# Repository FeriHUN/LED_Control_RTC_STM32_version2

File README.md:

# LED_Control_RTC_STM32_version2
20 channel 16 bit PWM LED strip brightness controller for 12-24V applications with RS485 connectivity

[Expander board link](https://github.com/FeriHUN/LED_Control_RTC_STM32_version2_Expander)

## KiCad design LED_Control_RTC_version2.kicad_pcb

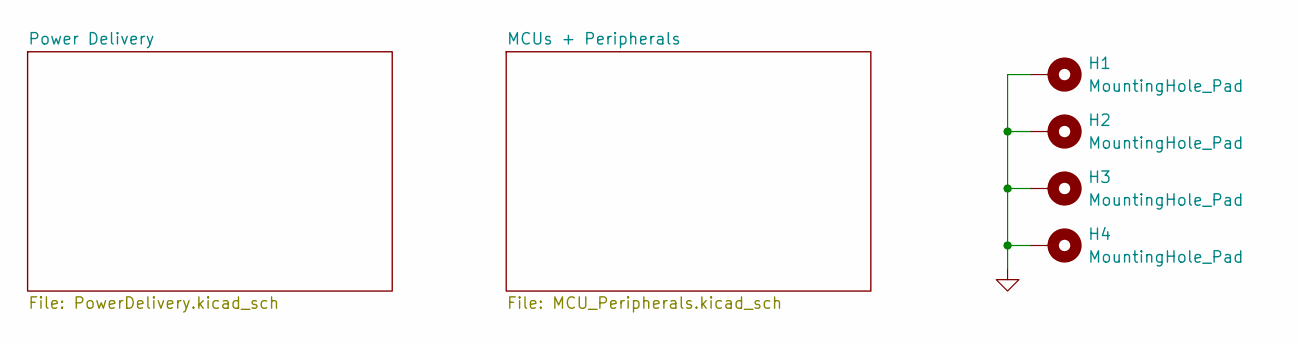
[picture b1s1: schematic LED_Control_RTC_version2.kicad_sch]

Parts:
H1, H2, H3, H4: MountingHole_Pad; MountingHole_3.2mm_M3_Pad_Via

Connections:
GND: H1.1, H2.1, H3.1, H4.1; also elsewhere on the board

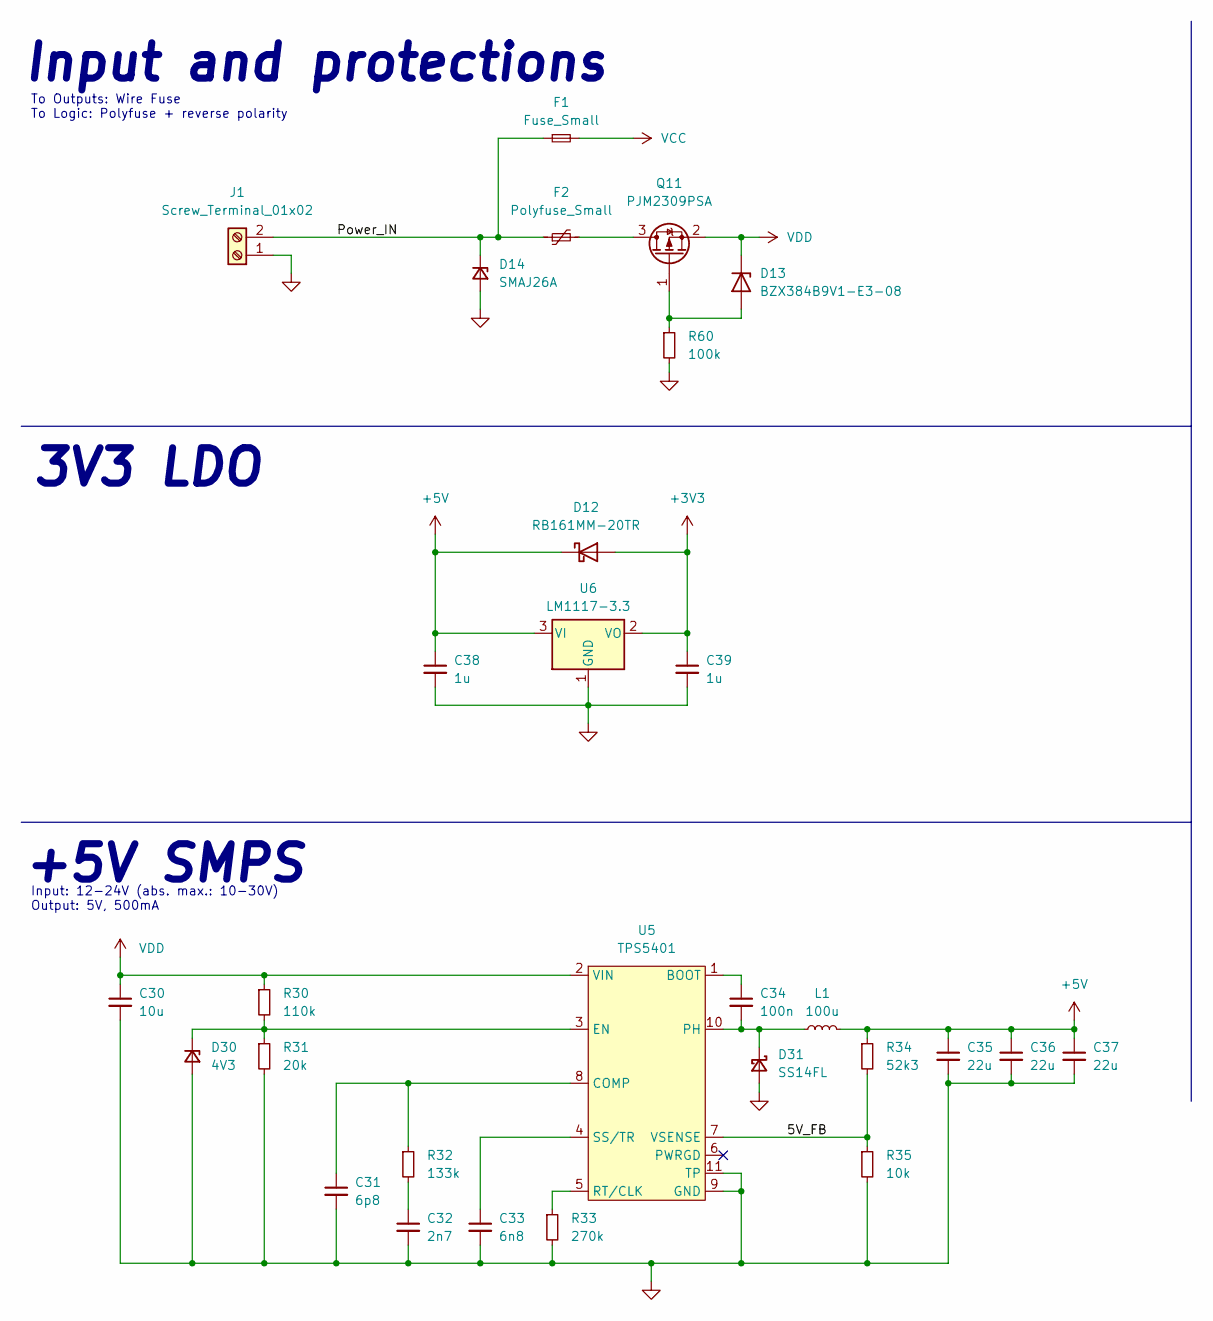
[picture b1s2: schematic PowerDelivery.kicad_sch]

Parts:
C30: 10u; R_1206_3216Metric
C31: 6p8; R_0603_1608Metric
C32: 2n7; R_0603_1608Metric
C33: 6n8; R_0603_1608Metric
C34: 100n; R_0603_1608Metric
C35, C36, C37: 22u; R_1206_3216Metric
C38, C39: 1u; C_0603_1608Metric
D12: RB161MM-20TR; D_SOD-123F
D13: BZX384B9V1-E3-08; D_SOD-323
D14: SMAJ26A; D_SMA
D30: 4V3; D_SOD-123
D31: SS14FL; D_SMA
F1: Fuse_Small; Fuseholder_Littelfuse_100_series_5x20mm
F2: Polyfuse_Small; Fuse_1812_4532Metric
J1: Screw_Terminal_01x02; PhoenixContact_MC_1,5_2-GF-5.08_1x02_P5.08mm_Horizontal_Thr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
L1: 100u; ABG08A40M101
Q11: PJM2309PSA; SOT-23
R30: 110k; R_0603_1608Metric
R31: 20k; R_0603_1608Metric
R32: 133k; R_0603_1608Metric
R33: 270k; R_0603_1608Metric
R34: 52k3; R_0603_1608Metric
R35: 10k; R_0603_1608Metric
R60: 100k; R_0402_1005Metric
U5: TPS5401; MSOP-10-1EP_3x3mm_P0.5mm_EP1.68x1.88mm_ThermalVias
U6: LM1117-3.3; SOT-223-3_TabPin2

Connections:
+5V: C35.1, C36.1, C37.1, C38.1, D12.1 (K), L1.2, R34.1, U6.3 (VI); also elsewhere on the board
/Power Delivery/5V_FB: R34.2, R35.1, U5.7 (VSENSE)
/Power Delivery/Power_IN: D14.1 (K), F1.1, F2.1, J1.2
GND: C30.2, C31.2, C32.2, C33.2, C35.2, C36.2, C37.2, C38.2, C39.2, D14.2 (A), D30.2 (A), D31.2 (A), J1.1, R31.2, R33.2, R35.2, R60.2, U5.9 (GND), U5.11 (TP), U6.1 (GND); also elsewhere on the board
unnamed: C31.1, R32.1, U5.8 (COMP)
unnamed: C32.1, R32.2
unnamed: C33.1, U5.4 (SS/TR)
unnamed: C34.1, U5.1 (BOOT)
unnamed: C34.2, D31.1 (K), L1.1, U5.10 (PH)
unnamed: D13.2 (A), Q11.1 (G), R60.1
unnamed: D30.1 (K), R30.2, R31.1, U5.3 (EN)
unnamed: F2.2, Q11.3 (D)
unnamed: R33.1, U5.5 (RT/CLK)
VCC: F1.2; also elsewhere on the board
VDD: C30.1, D13.1 (K), Q11.2 (S), R30.1, U5.2 (VIN)

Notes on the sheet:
+5V SMPS
Input: 12-24V (abs. max.: 10-30V) Output: 5V, 500mA
3V3 LDO
Input and protections
To Outputs: Wire Fuse To Logic: Polyfuse + reverse polarity

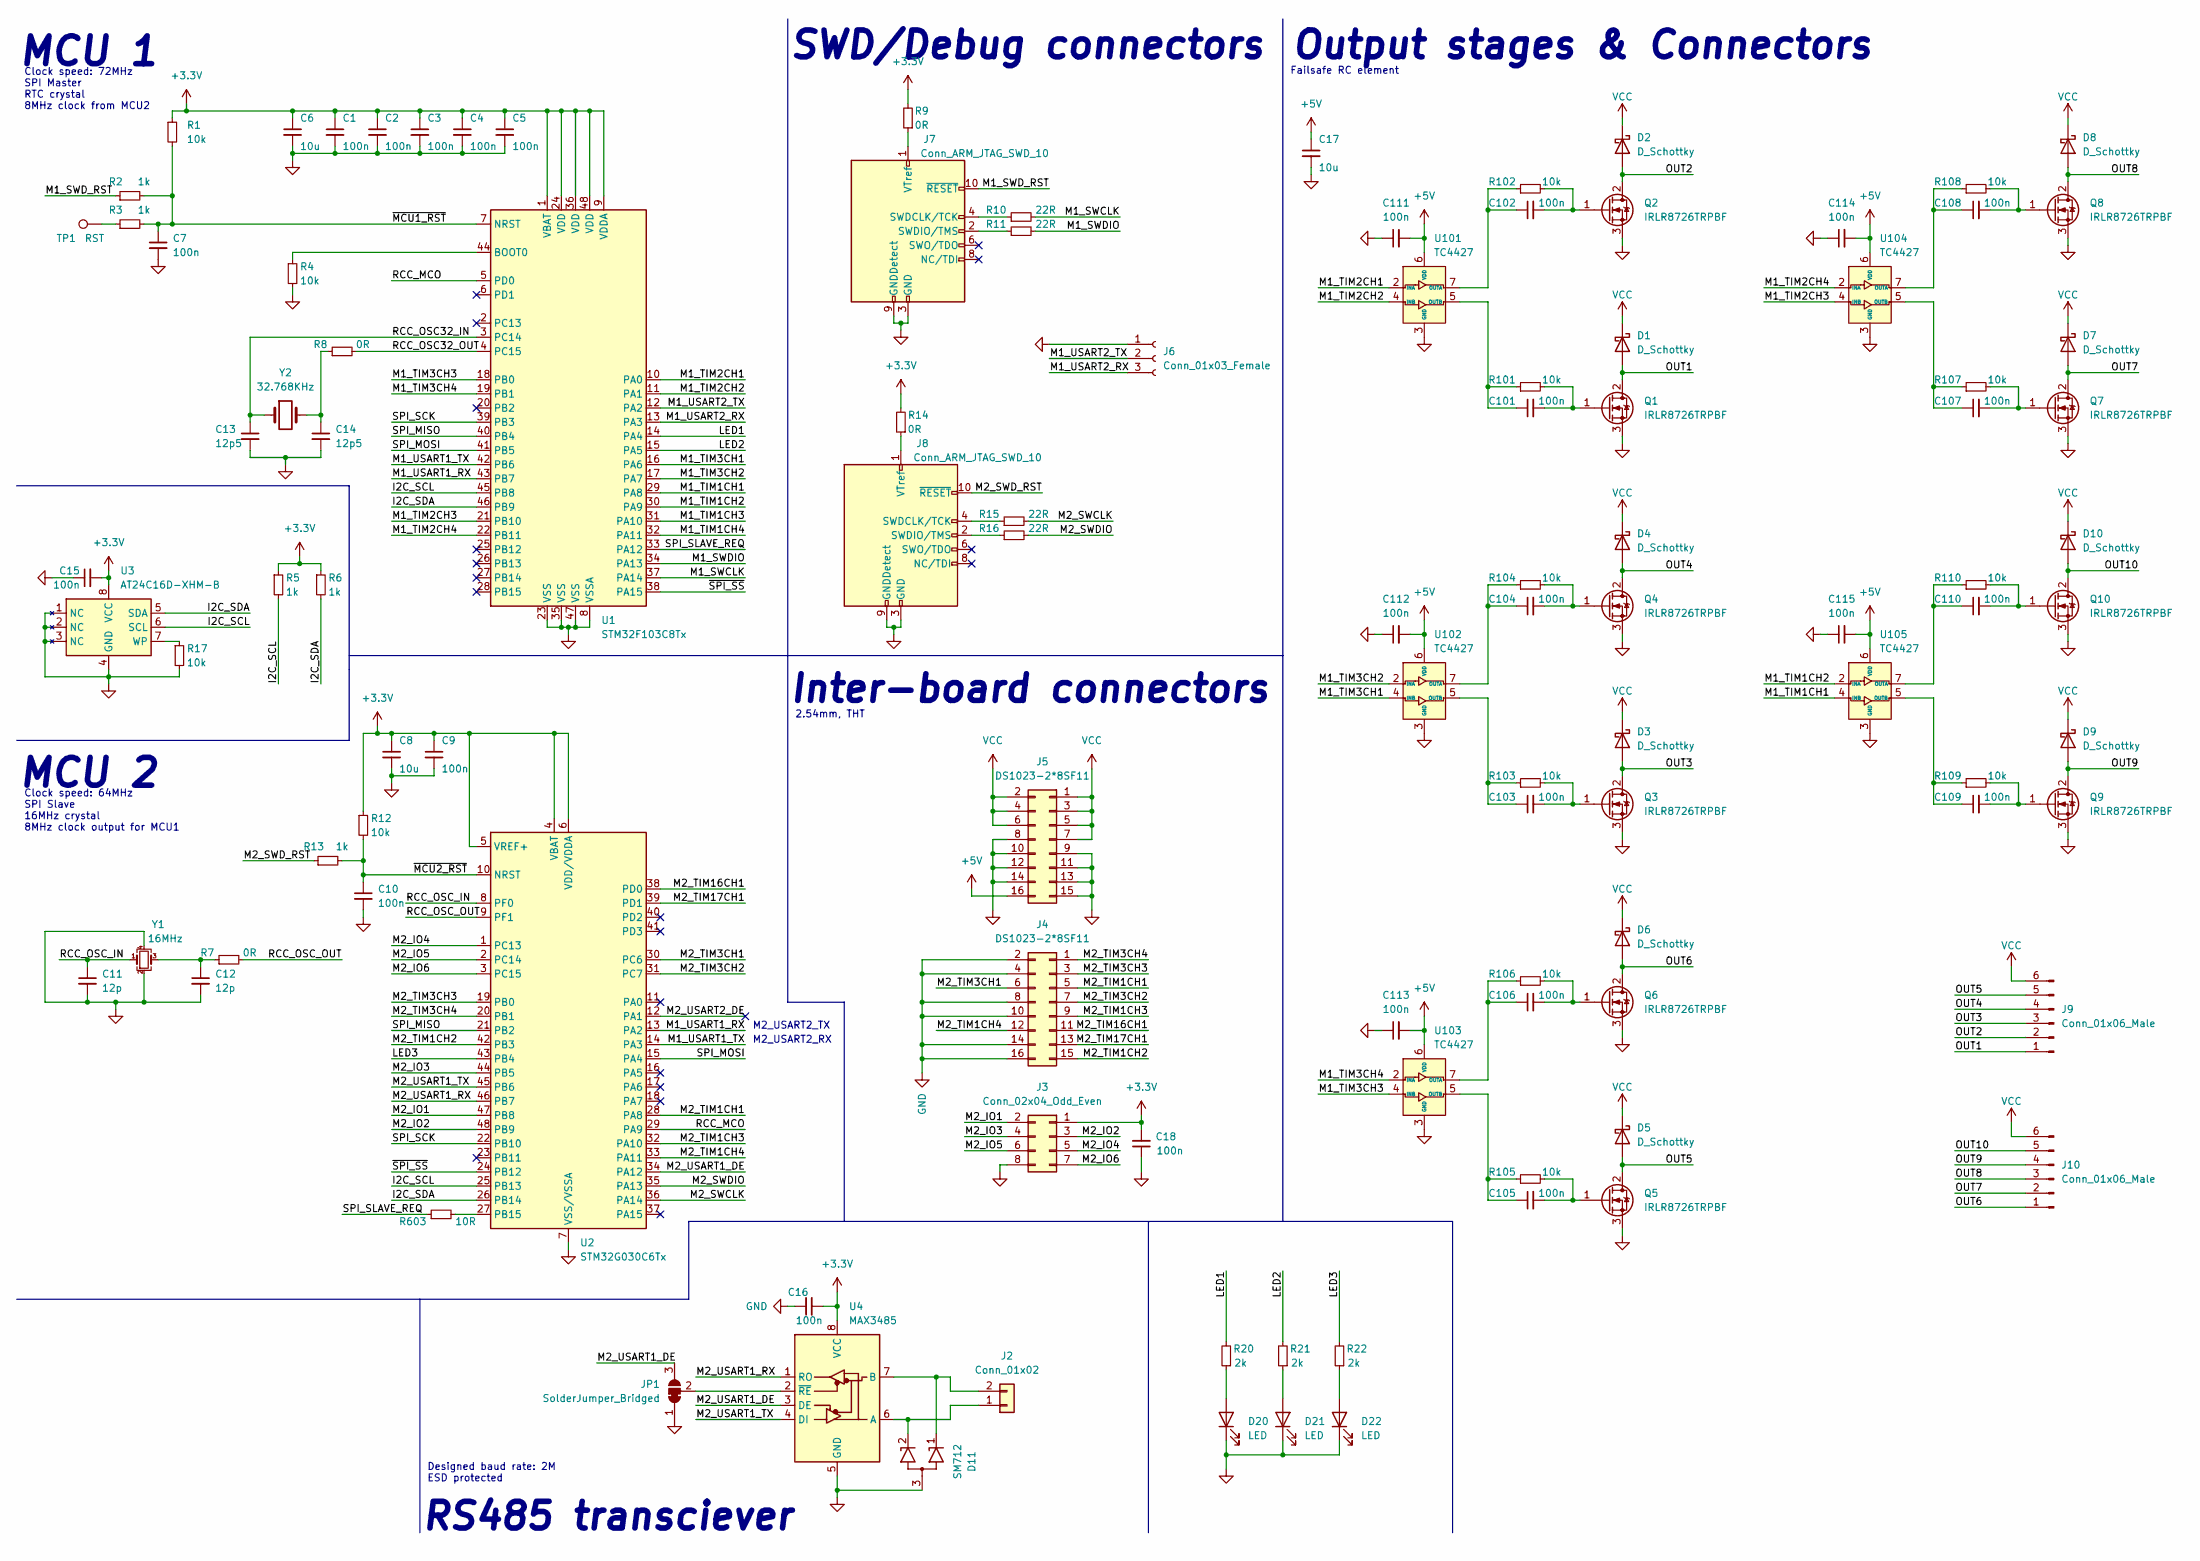
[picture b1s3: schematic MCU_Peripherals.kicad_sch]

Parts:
C1, C2, C3, C4, C5, C7, C9, C10, C15, C16, C18, C101, C102, C103, C104, C105, C106, C107, C108, C109, C110, C111, C112, C113, C114, C115: 100n; C_0402_1005Metric
C6, C8, C17: 10u; R_1206_3216Metric
C11, C12: 12p; C_0402_1005Metric
C13, C14: 12p5; C_0402_1005Metric
D1, D2, D3, D4, D5, D6, D7, D8, D9, D10: D_Schottky; D_SMA
D11: SM712; SOT-23
D20, D21, D22: LED; LED_1206_3216Metric
J2: Conn_01x02; DB2ERC-2.54-2P-GN
J3: Conn_02x04_Odd_Even; PinSocket_2x04_P2.54mm_Vertical
J4, J5: DS1023-2*8SF11; PinSocket_2x08_P2.54mm_Vertical
J6: Conn_01x03_Female; PinSocket_1x03_P2.54mm_Vertical
J7, J8: Conn_ARM_JTAG_SWD_10; PinHeader_2x05_P1.27mm_Vertical_SMD
J9, J10: Conn_01x06_Male; PhoenixContact_MCV_1,5_6-GF-3.81_1x06_P3.81mm_Vertical_Thre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
JP1: SolderJumper_Bridged; SolderJumper-3_P1.3mm_Bridged12_Pad1.0x1.5mm
Q1, Q2, Q3, Q4, Q5, Q6, Q7, Q8, Q9, Q10: IRLR8726TRPBF; TO-252-2
R1, R4, R12, R17, R101, R102, R103, R104, R105, R106, R107, R108, R109, R110: 10k; R_0402_1005Metric
R2, R3, R5, R6, R13: 1k; R_0402_1005Metric
R7, R8, R9, R14: 0R; R_0402_1005Metric
R10, R11, R15, R16: 22R; R_0402_1005Metric
R20, R21, R22: 2k; R_0402_1005Metric
R603: 10R; R_0402_1005Metric
TP1: RST; TestPoint_Pad_D1.0mm
U1: STM32F103C8Tx; LQFP-48_7x7mm_P0.5mm
U2: STM32G030C6Tx; LQFP-48_7x7mm_P0.5mm
U3: AT24C16D-XHM-B; TSSOP-8_4.4x3mm_P0.65mm
U4: MAX3485; SOP-8_3.9x4.9mm_P1.27mm
U101, U102, U103, U104, U105: TC4427; SOIC-8_3.9x4.9mm_P1.27mm
Y1: 16MHz; Crystal_SMD_3225-4Pin_3.2x2.5mm
Y2: 32.768KHz; Crystal_SMD_3215-2Pin_3.2x1.5mm

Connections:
+5V: C17.1, C111.2, C112.2, C113.2, C114.2, C115.2, J5.16, U101.6 (VDD), U102.6 (VDD), U103.6 (VDD), U104.6 (VDD), U105.6 (VDD); also elsewhere on the board
/MCUs + Peripherals/I2C_SCL: R5.2, U1.45 (PB8), U2.25 (PB13), U3.6 (SCL)
/MCUs + Peripherals/I2C_SDA: R6.2, U1.46 (PB9), U2.26 (PB14), U3.5 (SDA)
/MCUs + Peripherals/LED1: R20.2, U1.14 (PA4)
/MCUs + Peripherals/LED2: R21.2, U1.15 (PA5)
/MCUs + Peripherals/LED3: R22.2, U2.43 (PB4)
/MCUs + Peripherals/M1_SWCLK: R10.2, U1.37 (PA14)
/MCUs + Peripherals/M1_SWDIO: R11.2, U1.34 (PA13)
/MCUs + Peripherals/M1_SWD_RST: J7.10 (~RESET), R2.1
/MCUs + Peripherals/M1_TIM1CH1: U1.29 (PA8), U105.4 (INB)
/MCUs + Peripherals/M1_TIM1CH2: U1.30 (PA9), U105.2 (INA)
/MCUs + Peripherals/M1_TIM1CH3: U1.31 (PA10)
/MCUs + Peripherals/M1_TIM1CH4: U1.32 (PA11)
/MCUs + Peripherals/M1_TIM2CH1: U1.10 (PA0), U101.2 (INA)
/MCUs + Peripherals/M1_TIM2CH2: U1.11 (PA1), U101.4 (INB)
/MCUs + Peripherals/M1_TIM2CH3: U1.21 (PB10), U104.4 (INB)
/MCUs + Peripherals/M1_TIM2CH4: U1.22 (PB11), U104.2 (INA)
/MCUs + Peripherals/M1_TIM3CH1: U1.16 (PA6), U102.4 (INB)
/MCUs + Peripherals/M1_TIM3CH2: U1.17 (PA7), U102.2 (INA)
/MCUs + Peripherals/M1_TIM3CH3: U1.18 (PB0), U103.4 (INB)
/MCUs + Peripherals/M1_TIM3CH4: U1.19 (PB1), U103.2 (INA)
/MCUs + Peripherals/M1_USART1_RX: U1.43 (PB7), U2.13 (PA2)
/MCUs + Peripherals/M1_USART1_TX: U1.42 (PB6), U2.14 (PA3)
/MCUs + Peripherals/M1_USART2_RX: J6.3, U1.13 (PA3)
/MCUs + Peripherals/M1_USART2_TX: J6.2, U1.12 (PA2)
/MCUs + Peripherals/M2_IO1: J3.2, U2.47 (PB8)
/MCUs + Peripherals/M2_IO2: J3.3, U2.48 (PB9)
/MCUs + Peripherals/M2_IO3: J3.4, U2.44 (PB5)
/MCUs + Peripherals/M2_IO4: J3.5, U2.1 (PC13)
/MCUs + Peripherals/M2_IO5: J3.6, U2.2 (PC14)
/MCUs + Peripherals/M2_IO6: J3.7, U2.3 (PC15)
/MCUs + Peripherals/M2_SWCLK: R15.2, U2.36 (PA14)
/MCUs + Peripherals/M2_SWDIO: R16.2, U2.35 (PA13)
/MCUs + Peripherals/M2_SWD_RST: J8.10 (~RESET), R13.1
/MCUs + Peripherals/M2_TIM1CH1: J4.5, U2.28 (PA8)
/MCUs + Peripherals/M2_TIM1CH2: J4.15, U2.42 (PB3)
/MCUs + Peripherals/M2_TIM1CH3: J4.9, U2.32 (PA10)
/MCUs + Peripherals/M2_TIM1CH4: J4.12, U2.33 (PA11)
/MCUs + Peripherals/M2_TIM3CH1: J4.6, U2.30 (PC6)
/MCUs + Peripherals/M2_TIM3CH2: J4.7, U2.31 (PC7)
/MCUs + Peripherals/M2_TIM3CH3: J4.3, U2.19 (PB0)
/MCUs + Peripherals/M2_TIM3CH4: J4.1, U2.20 (PB1)
/MCUs + Peripherals/M2_TIM16CH1: J4.11, U2.38 (PD0)
/MCUs + Peripherals/M2_TIM17CH1: J4.13, U2.39 (PD1)
/MCUs + Peripherals/M2_USART1_DE: JP1.3 (B), U2.34 (PA12), U4.3 (DE)
/MCUs + Peripherals/M2_USART1_RX: U2.46 (PB7), U4.1 (RO)
/MCUs + Peripherals/M2_USART1_TX: U2.45 (PB6), U4.4 (DI)
/MCUs + Peripherals/M2_USART2_DE: U2.12 (PA1)
/MCUs + Peripherals/OUT1: D1.2 (A), J9.1, Q1.2 (D)
/MCUs + Peripherals/OUT2: D2.2 (A), J9.2, Q2.2 (D)
/MCUs + Peripherals/OUT3: D3.2 (A), J9.3, Q3.2 (D)
/MCUs + Peripherals/OUT4: D4.2 (A), J9.4, Q4.2 (D)
/MCUs + Peripherals/OUT5: D5.2 (A), J9.5, Q5.2 (D)
/MCUs + Peripherals/OUT6: D6.2 (A), J10.1, Q6.2 (D)
/MCUs + Peripherals/OUT7: D7.2 (A), J10.2, Q7.2 (D)
/MCUs + Peripherals/OUT8: D8.2 (A), J10.3, Q8.2 (D)
/MCUs + Peripherals/OUT9: D9.2 (A), J10.4, Q9.2 (D)
/MCUs + Peripherals/OUT10: D10.2 (A), J10.5, Q10.2 (D)
/MCUs + Peripherals/RCC_MCO: U1.5 (PD0), U2.29 (PA9)
/MCUs + Peripherals/RCC_OSC32_IN: C13.1, U1.3 (PC14), Y2.1
/MCUs + Peripherals/RCC_OSC32_OUT: R8.2, U1.4 (PC15)
/MCUs + Peripherals/RCC_OSC_IN: C11.1, U2.8 (PF0), Y1.1
/MCUs + Peripherals/RCC_OSC_OUT: R7.2, U2.9 (PF1)
/MCUs + Peripherals/SPI_MISO: U1.40 (PB4), U2.21 (PB2)
/MCUs + Peripherals/SPI_MOSI: U1.41 (PB5), U2.15 (PA4)
/MCUs + Peripherals/SPI_SCK: U1.39 (PB3), U2.22 (PB10)
/MCUs + Peripherals/SPI_SLAVE_REQ: R603.1, U1.33 (PA12)
/MCUs + Peripherals/~MCU1_RST: C7.1, R1.2, R2.2, R3.2, U1.7 (NRST)
/MCUs + Peripherals/~MCU2_RST: C10.1, R12.2, R13.2, U2.10 (NRST)
/MCUs + Peripherals/~SPI_SS: U1.38 (PA15), U2.24 (PB12)
GND: C1.2, C2.2, C3.2, C4.2, C5.2, C6.2, C7.2, C8.2, C9.2, C10.2, C11.2, C12.2, C13.2, C14.2, C15.1, C16.1, C17.2, C18.1, C111.1, C112.1, C113.1, C114.1, C115.1, D11.3 (A), D20.1 (K), D21.1 (K), D22.1 (K), J3.8, J4.2, J4.4, J4.8, J4.10, J4.14, J4.16, J5.8, J5.9, J5.10, J5.11, J5.12, J5.13, J5.14, J5.15, J6.1, J7.3 (GND), J7.5 (GND), J7.9 (GNDDetect), J8.3 (GND), J8.5 (GND), J8.9 (GNDDetect), JP1.1 (A), Q1.3 (S), Q2.3 (S), Q3.3 (S), Q4.3 (S), Q5.3 (S), Q6.3 (S), Q7.3 (S), Q8.3 (S), Q9.3 (S), Q10.3 (S), R4.2, R17.2, U1.8 (VSSA), U1.23 (VSS), U1.35 (VSS), U1.47 (VSS), U2.7 (VSS/VSSA), U3.1 (NC), U3.2 (NC), U3.3 (NC), U3.4 (GND), U4.5 (GND), U101.3 (GND), U102.3 (GND), U103.3 (GND), U104.3 (GND), U105.3 (GND), Y1.2, Y1.4; also elsewhere on the board
unnamed: C12.1, R7.1, Y1.3
unnamed: C14.1, R8.1, Y2.2
unnamed: C101.1, R101.1, U101.5 (OUTB)
unnamed: C101.2, Q1.1 (G), R101.2
unnamed: C102.1, R102.1, U101.7 (OUTA)
unnamed: C102.2, Q2.1 (G), R102.2
unnamed: C103.1, R103.1, U102.5 (OUTB)
unnamed: C103.2, Q3.1 (G), R103.2
unnamed: C104.1, R104.1, U102.7 (OUTA)
unnamed: C104.2, Q4.1 (G), R104.2
unnamed: C105.1, R105.1, U103.5 (OUTB)
unnamed: C105.2, Q5.1 (G), R105.2
unnamed: C106.1, R106.1, U103.7 (OUTA)
unnamed: C106.2, Q6.1 (G), R106.2
unnamed: C107.1, R107.1, U104.5 (OUTB)
unnamed: C107.2, Q7.1 (G), R107.2
unnamed: C108.1, R108.1, U104.7 (OUTA)
unnamed: C108.2, Q8.1 (G), R108.2
unnamed: C109.1, R109.1, U105.5 (OUTB)
unnamed: C109.2, Q9.1 (G), R109.2
unnamed: C110.1, R110.1, U105.7 (OUTA)
unnamed: C110.2, Q10.1 (G), R110.2
unnamed: D11.1 (K1), J2.2, U4.7 (B)
unnamed: D11.2 (K2), J2.1, U4.6 (A)
unnamed: D20.2 (A), R20.1
unnamed: D21.2 (A), R21.1
unnamed: D22.2 (A), R22.1
unnamed: J7.1 (VTref), R9.1
unnamed: J7.2 (SWDIO/TMS), R11.1
unnamed: J7.4 (SWDCLK/TCK), R10.1
unnamed: J8.1 (VTref), R14.1
unnamed: J8.2 (SWDIO/TMS), R16.1
unnamed: J8.4 (SWDCLK/TCK), R15.1
unnamed: JP1.2 (C), U4.2 (~RE)
unnamed: R3.1, TP1.1
unnamed: R4.1, U1.44 (BOOT0)
unnamed: R17.1, U3.7 (WP)
unnamed: R603.2, U2.27 (PB15)
VCC: D1.1 (K), D2.1 (K), D3.1 (K), D4.1 (K), D5.1 (K), D6.1 (K), D7.1 (K), D8.1 (K), D9.1 (K), D10.1 (K), J5.1, J5.2, J5.3, J5.4, J5.5, J5.6, J5.7, J9.6, J10.6; also elsewhere on the board

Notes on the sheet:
Failsafe RC element
Inter-board connectors
Clock speed: 72MHz SPI Master RTC crystal 8MHz clock from MCU2
Clock speed: 64MHz SPI Slave 16MHz crystal 8MHz clock output for MCU1
M2_USART2_TX
SWD/Debug connectors
MCU 1
RS485 transciever
2.54mm, THT
Designed baud rate: 2M ESD protected
Output stages & Connectors
M2_USART2_RX
MCU 2

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
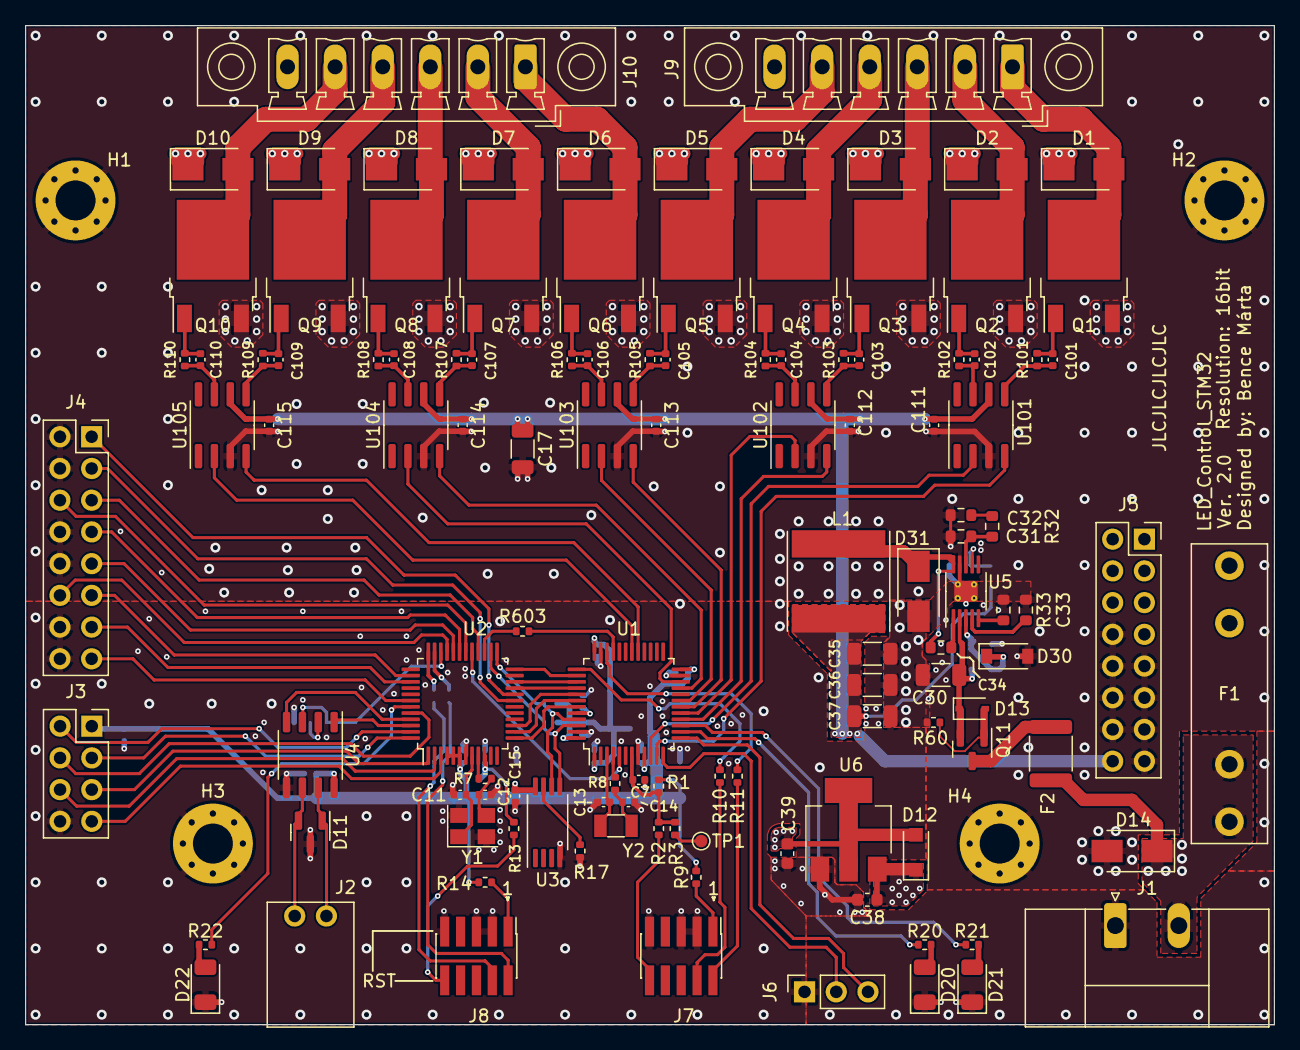
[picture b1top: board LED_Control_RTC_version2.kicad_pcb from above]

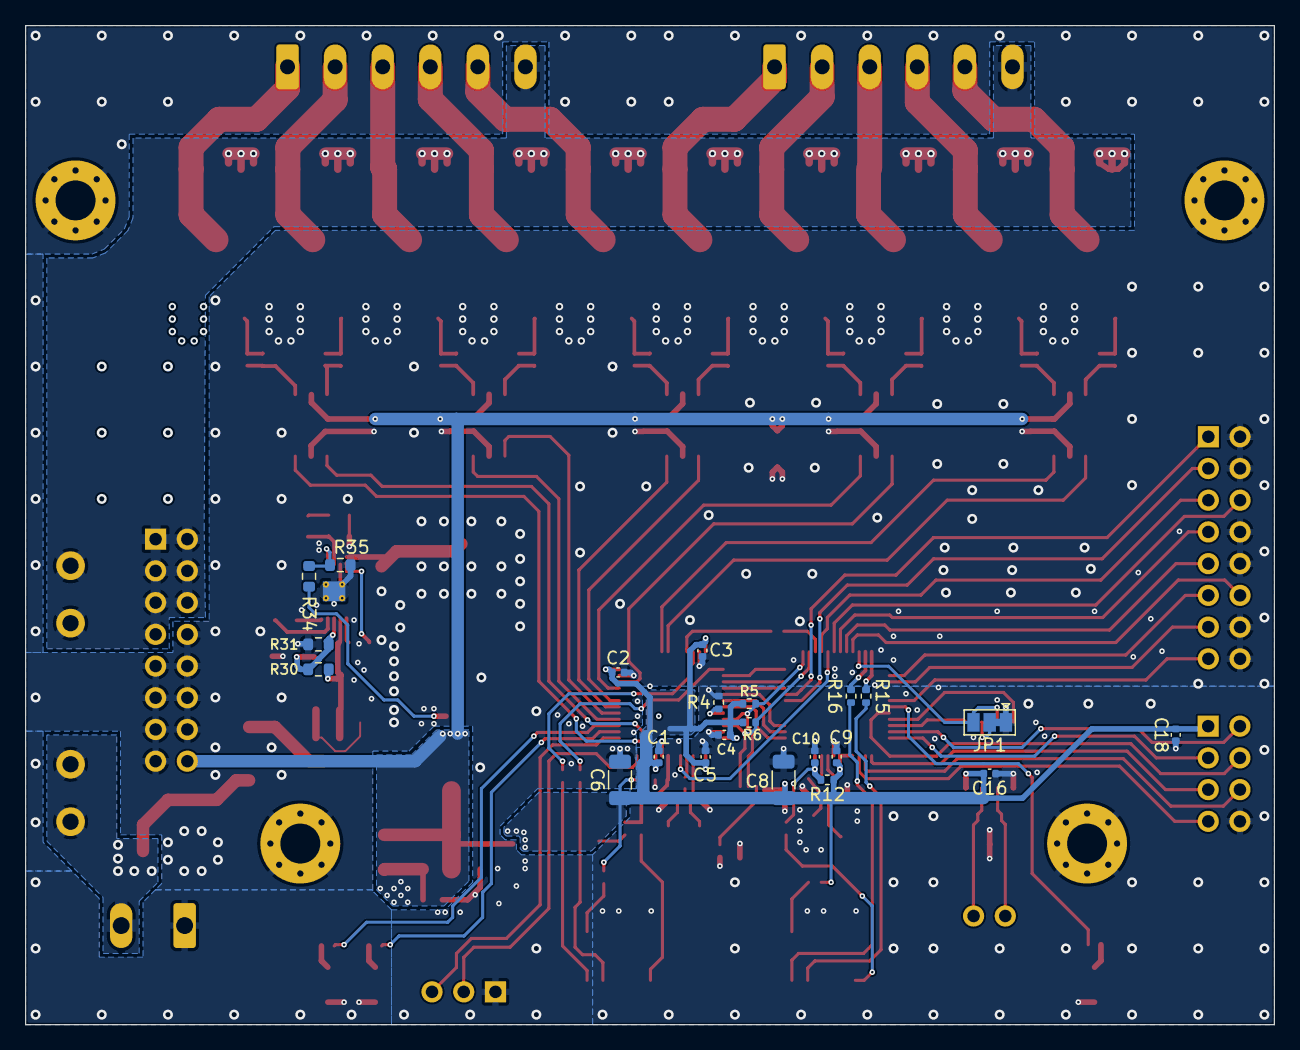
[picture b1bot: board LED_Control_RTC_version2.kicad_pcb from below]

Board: 4 copper layers, 100.0 x 80.0 mm, 143 parts (22 on the bottom side), 120 nets.

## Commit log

2022-09-09 INitial files commit
2022-09-10 Cleaned up messy reference numbering Added labels to schematic
2022-09-10 Added TVS diode on power input
2022-09-11 Added more GND vias
2022-09-13 Added FET driver cap
2022-09-16 Ready for prod
2022-09-18 Added interactive BOM (bom/ibom.html)
2022-10-05 Corrected bad footprint of RS485 connector
